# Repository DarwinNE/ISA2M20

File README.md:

# ISA2M20
Adapter for 8-bit ISA card for the Olivetti M20

This project is dedicated to an adapter that allows to connect 8 bit ISA boards to
the bus of an Olivetti M20. Yes, we are talking about 1982 technology.
That may allow to do some nice stuff on the M20 as long as you are able to write the
software for the cards you want to attach.

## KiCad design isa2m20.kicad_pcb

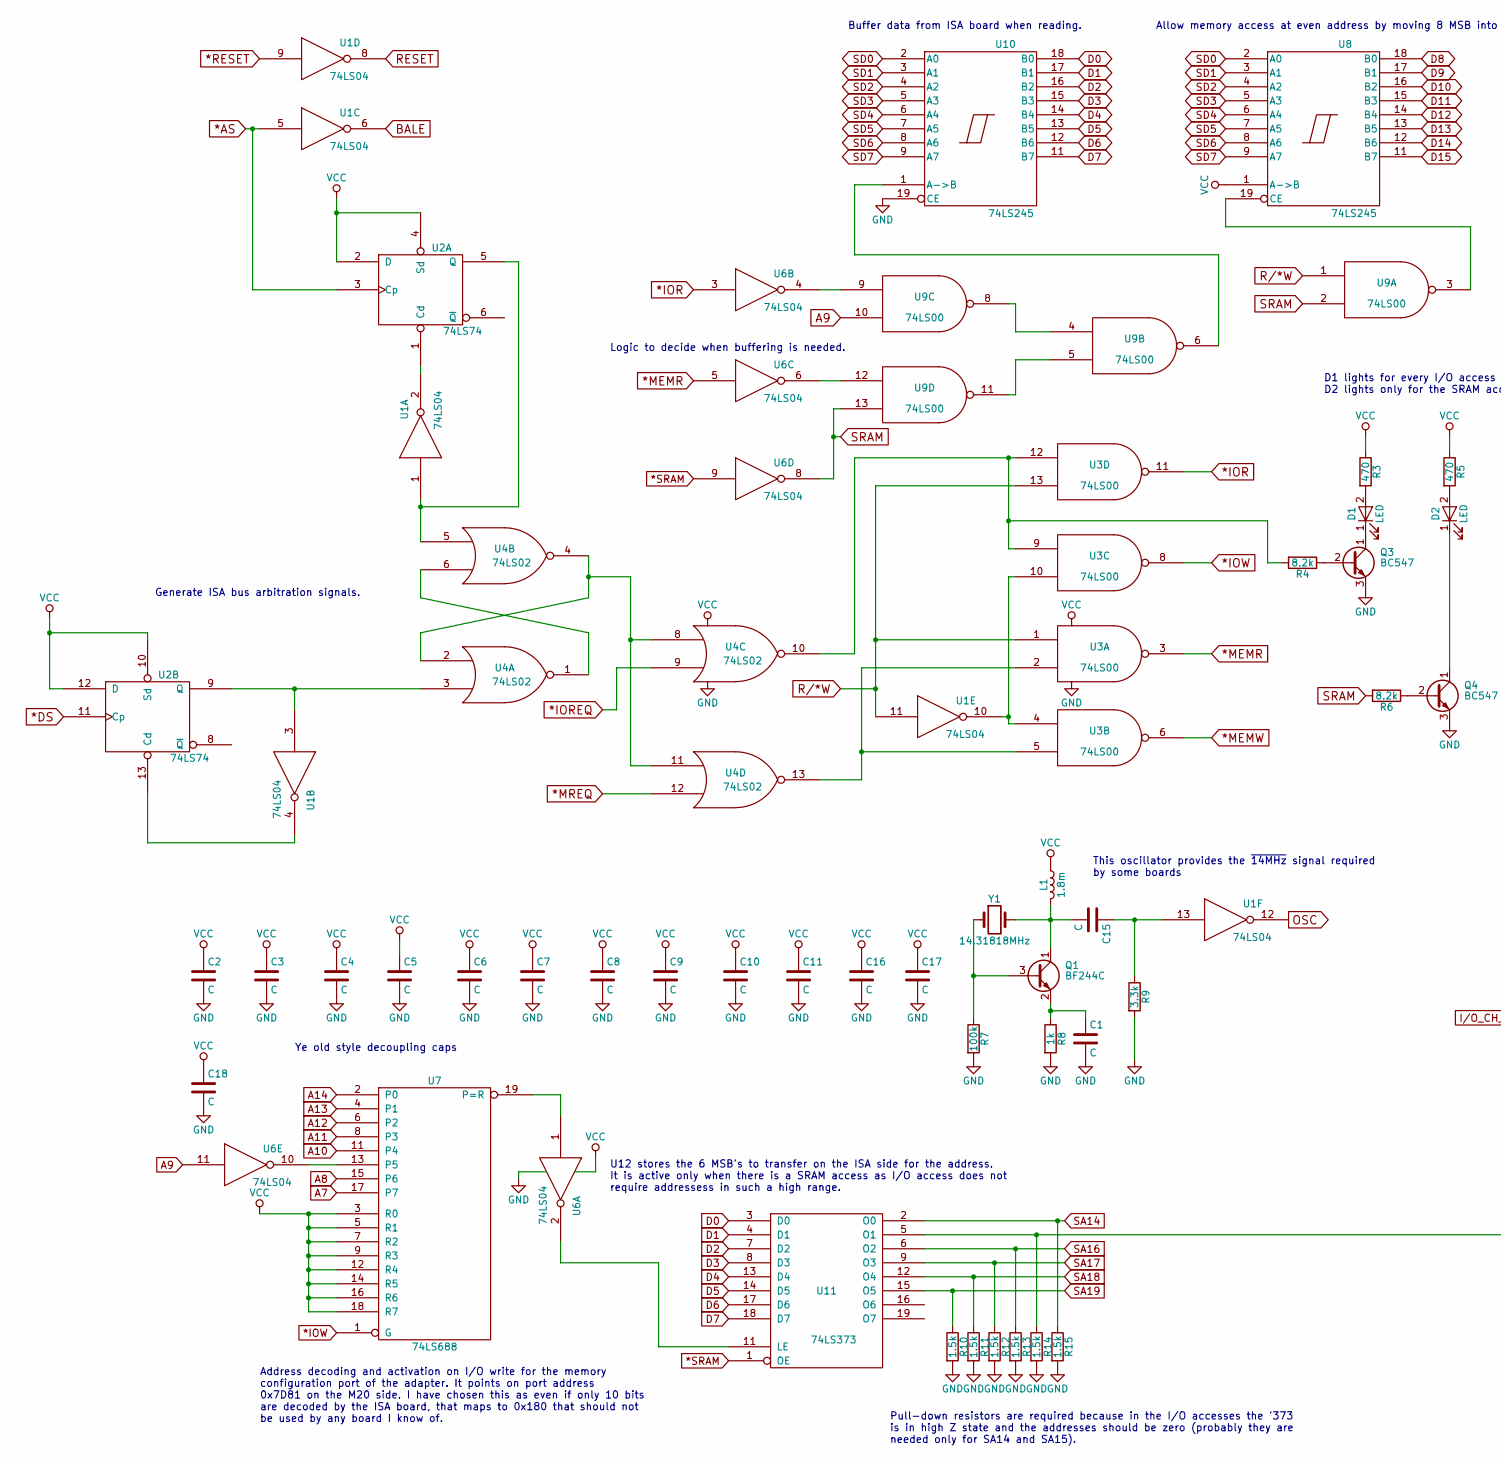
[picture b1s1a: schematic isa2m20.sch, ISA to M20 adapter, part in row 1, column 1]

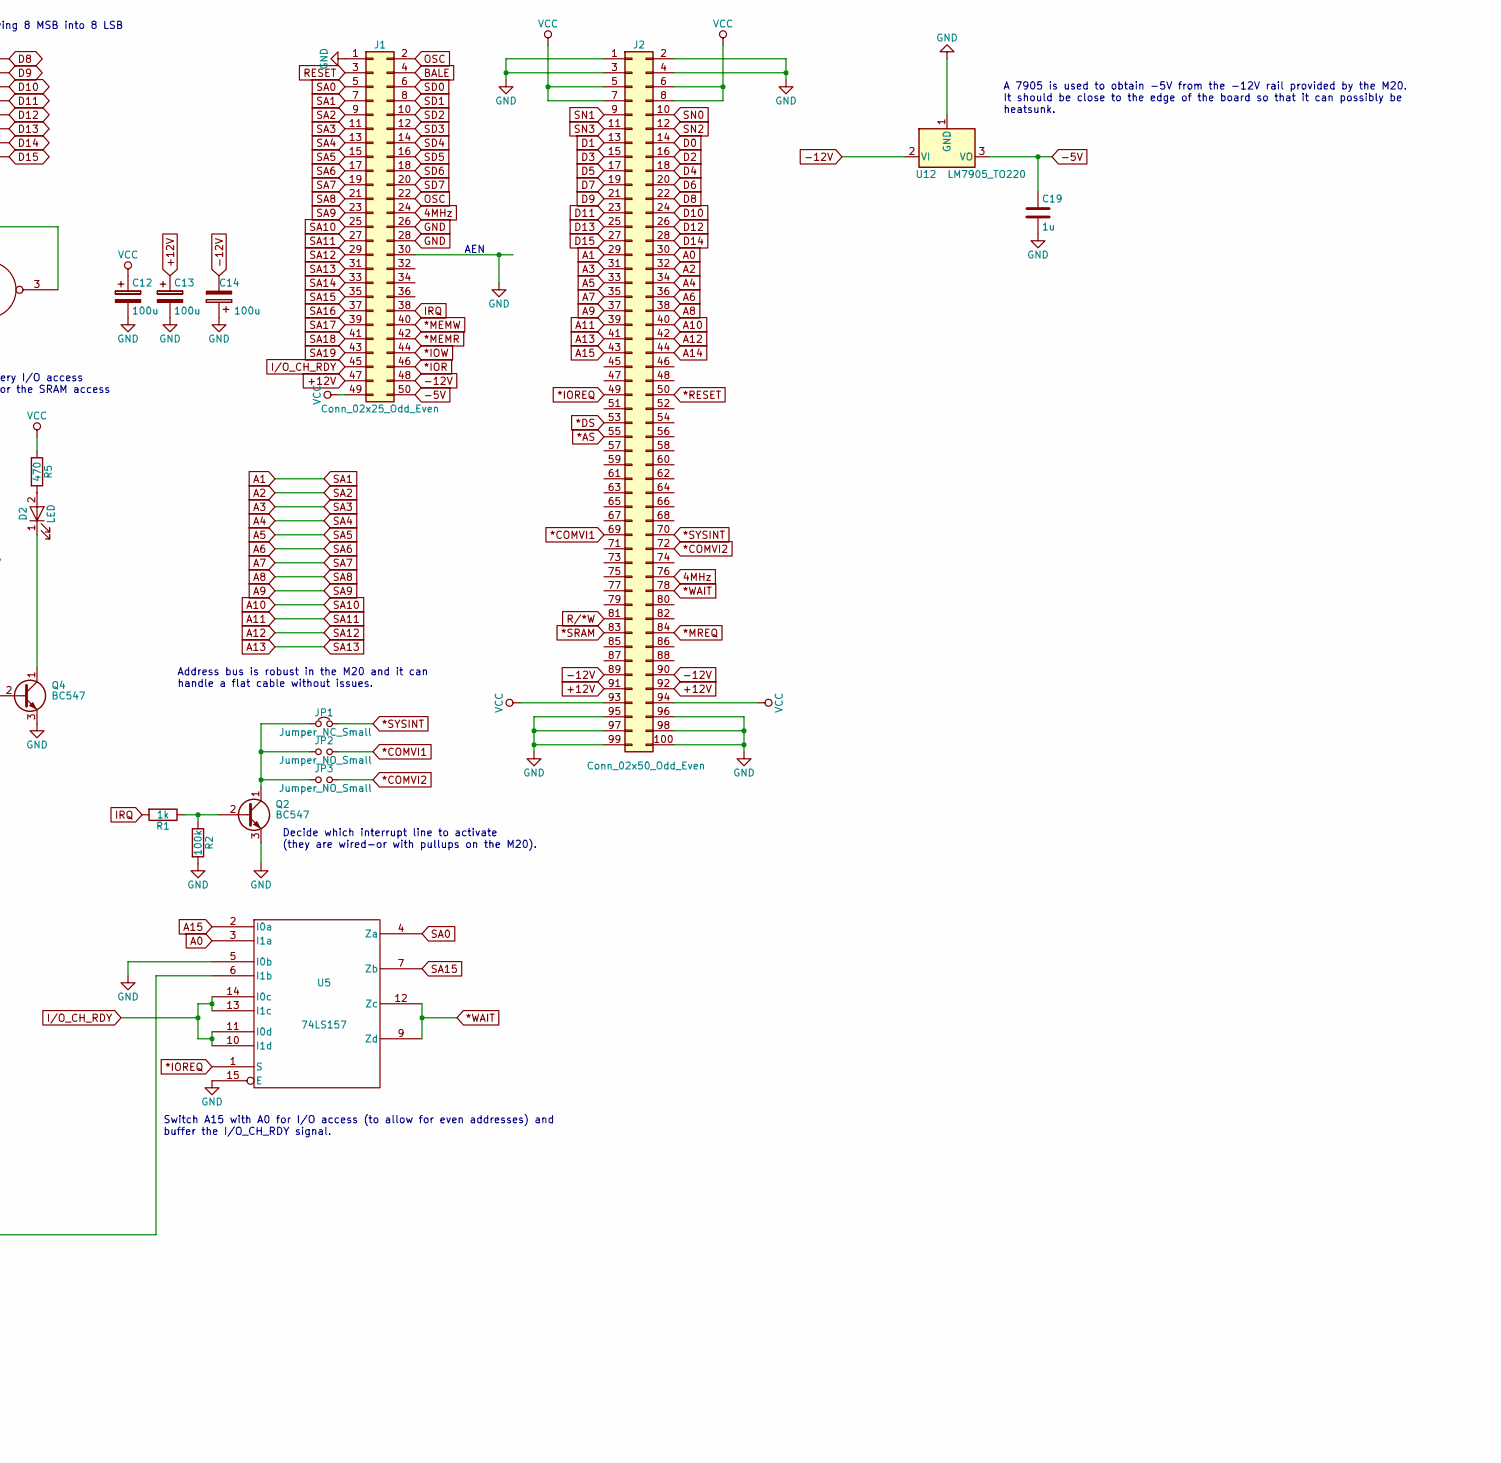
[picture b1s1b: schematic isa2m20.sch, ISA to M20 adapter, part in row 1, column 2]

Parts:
C1: C; C_Axial_L5.1mm_D3.1mm_P7.50mm_Horizontal
C2, C3, C4, C5, C6, C7, C8, C9, C10, C11, C15, C16, C17, C18: C; C_Rect_L9.0mm_W2.5mm_P7.50mm_MKT
C12, C13, C14: 100u; CP_Radial_D10.0mm_P5.00mm
C19: 1u; C_Rect_L9.0mm_W2.5mm_P7.50mm_MKT
D1, D2: LED; LED_D3.0mm
J1: Conn_02x25_Odd_Even; Multicomp_MC9A12-5034_2x25x2.54mm_Straight
J2: Conn_02x50_Odd_Even; 2x50pin_PCB_edge_connector
JP1: Jumper_NC_Small; Socket_Strip_Straight_1x02_Pitch2.54mm
JP2, JP3: Jumper_NO_Small; Socket_Strip_Straight_1x02_Pitch2.54mm
L1: 1.8m; L_Radial_D7.5mm_P5.00mm_Fastron_07P
Q1: BF244C; TO-92_Molded_Narrow
Q2, Q3, Q4: BC547; TO-92_Molded_Narrow
R1, R8: 1k; R_Axial_DIN0207_L6.3mm_D2.5mm_P7.62mm_Horizontal
R2, R7: 100k; R_Axial_DIN0207_L6.3mm_D2.5mm_P7.62mm_Horizontal
R3, R5: 470; R_Axial_DIN0207_L6.3mm_D2.5mm_P7.62mm_Horizontal
R4, R6: 8.2k; R_Axial_DIN0207_L6.3mm_D2.5mm_P7.62mm_Horizontal
R9: 3.3k; R_Axial_DIN0207_L6.3mm_D2.5mm_P7.62mm_Horizontal
R10, R11, R12, R13, R14, R15: 1.5k; R_Axial_DIN0207_L6.3mm_D2.5mm_P7.62mm_Horizontal
U1, U6: 74LS04; DIP-14_W7.62mm_Socket_LongPads
U2: 74LS74; DIP-14_W7.62mm_Socket_LongPads
U3, U9: 74LS00; DIP-14_W7.62mm_Socket_LongPads
U4: 74LS02; DIP-14_W7.62mm_Socket_LongPads
U5: 74LS157; DIP-16_W7.62mm_Socket_LongPads
U7: 74LS688; DIP-20_W7.62mm_Socket_LongPads
U8, U10: 74LS245; DIP-20_W7.62mm_Socket_LongPads
U11: 74LS373; DIP-20_W7.62mm_Socket_LongPads
U12: LM7905_TO220; TO-220-3_Vertical
Y1: 14.31818MHz; Crystal_HC18-U_Vertical

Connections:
4MHz: J1.24, J2.76
*AS: J2.55, U1.5, U2.3 (Cp)
*COMVI1: J2.69, JP2.2
*COMVI2: J2.72, JP3.2
*DS: J2.53, U2.11 (Cp)
*IOR: J1.46, U3.11, U6.3
*IOREQ: J2.49, U4.9, U5.1 (S)
*IOW: J1.44, U3.8, U7.1 (G)
*MEMR: J1.42, U3.3, U6.5
*MEMW: J1.40, U3.6
*MREQ: J2.84, U4.12
*RESET: J2.50, U1.9
*SRAM: J2.83, U6.9, U11.1 (OE)
*SYSINT: J2.70, JP1.2
*WAIT: J2.78, U5.9 (Zd), U5.12 (Zc)
+12V: C13.1, J1.47, J2.91, J2.92
-5V: C19.1, J1.50, U12.3 (VO)
-12V: C14.2, J1.48, J2.89, J2.90, U12.2 (VI)
A0: J2.30, U5.3 (I1a)
A1: J1.7, J2.29
A2: J1.9, J2.32
A3: J1.11, J2.31
A4: J1.13, J2.34
A5: J1.15, J2.33
A6: J1.17, J2.36
A7: J1.19, J2.35, U7.17 (P7)
A8: J1.21, J2.38, U7.15 (P6)
A9: J1.23, J2.37, U6.11, U9.10
A10: J1.25, J2.40, U7.11 (P4)
A11: J1.27, J2.39, U7.8 (P3)
A12: J1.29, J2.42, U7.6 (P2)
A13: J1.31, J2.41, U7.4 (P1)
A14: J2.44, U7.2 (P0)
A15: J2.43, U5.2 (I0a)
BALE: J1.4, U1.6
D0: J2.14, U10.18 (B0), U11.3 (D0)
D1: J2.13, U10.17 (B1), U11.4 (D1)
D2: J2.16, U10.16 (B2), U11.7 (D2)
D3: J2.15, U10.15 (B3), U11.8 (D3)
D4: J2.18, U10.14 (B4), U11.13 (D4)
D5: J2.17, U10.13 (B5), U11.14 (D5)
D6: J2.20, U10.12 (B6), U11.17 (D6)
D7: J2.19, U10.11 (B7), U11.18 (D7)
D8: J2.22, U8.18 (B0)
D9: J2.21, U8.17 (B1)
D10: J2.24, U8.16 (B2)
D11: J2.23, U8.15 (B3)
D12: J2.26, U8.14 (B4)
D13: J2.25, U8.13 (B5)
D14: J2.28, U8.12 (B6)
D15: J2.27, U8.11 (B7)
GND: C1.2, C2.2, C3.2, C4.2, C5.2, C6.2, C7.2, C8.2, C9.2, C10.2, C11.2, C12.2, C13.2, C14.1, C16.2, C17.2, C18.2, C19.2, J1.1, J1.26, J1.28, J1.30, J2.1, J2.2, J2.3, J2.4, J2.95, J2.96, J2.97, J2.98, J2.99, J2.100, Q2.3 (E), Q3.3 (E), Q4.3 (E), R2.2, R7.2, R8.2, R9.2, R10.2, R11.2, R12.2, R13.2, R14.2, R15.2, U1.7 (GND), U2.7 (GND), U3.7 (GND), U4.7 (GND), U5.5 (I0b), U5.8 (GND), U5.15 (E), U6.7 (GND), U7.10 (GND), U8.10 (GND), U9.7 (GND), U10.10 (GND), U10.19 (CE), U11.10 (GND), U12.1 (GND)
I/O_CH_RDY: J1.45, U5.10 (I1d), U5.11 (I0d), U5.13 (I1c), U5.14 (I0c)
IRQ: J1.38, R1.2
unnamed: C1.1, Q1.2 (E), R8.1
unnamed: C15.1, R9.1, U1.13
unnamed: C15.2, L1.2, Q1.1 (C), Y1.2
unnamed: D1.1 (K), Q3.1 (C)
unnamed: D1.2 (A), R3.2
unnamed: D2.1 (K), Q4.1 (C)
unnamed: D2.2 (A), R5.2
unnamed: JP1.1, JP2.1, JP3.1, Q2.1 (C)
unnamed: Q1.3 (B), R7.1, Y1.1
unnamed: Q2.2 (B), R1.1, R2.1
unnamed: Q3.2 (B), R4.1
unnamed: Q4.2 (B), R6.1
unnamed: R4.2, U3.9, U3.12, U4.10
unnamed: R14.1, U5.6 (I1b), U11.5 (O1)
unnamed: U1.1, U2.5 (Q), U4.5
unnamed: U1.2, U2.1 (Cd)
unnamed: U1.3, U2.9 (Q), U4.3
unnamed: U1.4, U2.13 (Cd)
unnamed: U1.10, U3.4, U3.10
unnamed: U3.2, U3.5, U4.13
unnamed: U4.1, U4.6
unnamed: U4.2, U4.4, U4.8, U4.11
unnamed: U6.1, U7.19 (P=R)
unnamed: U6.4, U9.9
unnamed: U6.6, U9.12
unnamed: U6.10, U7.13 (P5)
unnamed: U8.19 (CE), U9.3
unnamed: U9.4, U9.8
unnamed: U9.5, U9.11
unnamed: U9.6, U10.1 (A->B)
unnamed: U6.2, U11.11 (LE)
OSC: J1.2, J1.22, U1.12
R/*W: J2.81, U1.11, U3.1, U3.13, U9.1
RESET: J1.3, U1.8
SA0: J1.5, U5.4 (Za)
SA14: J1.33, R15.1, U11.2 (O0)
SA15: J1.35, U5.7 (Zb)
SA16: J1.37, R13.1, U11.6 (O2)
SA17: J1.39, R12.1, U11.9 (O3)
SA18: J1.41, R11.1, U11.12 (O4)
SA19: J1.43, R10.1, U11.15 (O5)
SD0: J1.6, U8.2 (A0), U10.2 (A0)
SD1: J1.8, U8.3 (A1), U10.3 (A1)
SD2: J1.10, U8.4 (A2), U10.4 (A2)
SD3: J1.12, U8.5 (A3), U10.5 (A3)
SD4: J1.14, U8.6 (A4), U10.6 (A4)
SD5: J1.16, U8.7 (A5), U10.7 (A5)
SD6: J1.18, U8.8 (A6), U10.8 (A6)
SD7: J1.20, U8.9 (A7), U10.9 (A7)
SN0: J2.10
SN1: J2.9
SN2: J2.12
SN3: J2.11
SRAM: R6.2, U6.8, U9.2, U9.13
VCC: C2.1, C3.1, C4.1, C5.1, C6.1, C7.1, C8.1, C9.1, C10.1, C11.1, C12.1, C16.1, C17.1, C18.1, J1.49, J2.5, J2.6, J2.7, J2.8, J2.93, J2.94, L1.1, R3.1, R5.1, U1.14 (VCC), U2.2 (D), U2.4 (Sd), U2.10 (Sd), U2.12 (D), U2.14 (VCC), U3.14 (VCC), U4.14 (VCC), U5.16 (VCC), U6.14 (VCC), U7.3 (R0), U7.5 (R1), U7.7 (R2), U7.9 (R3), U7.12 (R4), U7.14 (R5), U7.16 (R6), U7.18 (R7), U7.20 (VCC), U8.1 (A->B), U8.20 (VCC), U9.14 (VCC), U10.20 (VCC), U11.20 (VCC)

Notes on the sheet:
A 7905 is used to obtain -5V from the -12V rail provided by the M20. It should be close to the edge of the board so that it can possibly be heatsunk.
This oscillator provides the ~14MHz signal required by some boards
D1 lights for every I/O access D2 lights only for the SRAM access
U12 stores the 6 MSB's to transfer on the ISA side for the address. It is active only when there is a SRAM access as I/O access does not require addressess in such a high range.
Address decoding and activation on I/O write for the memory configuration port of the adapter. It points on port address 0x7D81 on the M20 side. I have chosen this as even if only 10 bits are decoded by the ISA board, that maps to 0x180 that should not be used by any board I know of.
Pull-down resistors are required because in the I/O accesses the '373 is in high Z state and the addresses should be zero (probably they are needed only for SA14 and SA15).
Ye old style decoupling caps
Allow memory access at even address by moving 8 MSB into 8 LSB
Buffer data from ISA board when reading.
Logic to decide when buffering is needed.
Generate ISA bus arbitration signals.
Address bus is robust in the M20 and it can handle a flat cable without issues.
Decide which interrupt line to activate (they are wired-or with pullups on the M20).
Switch A15 with A0 for I/O access (to allow for even addresses) and buffer the I/O_CH_RDY signal.
AEN

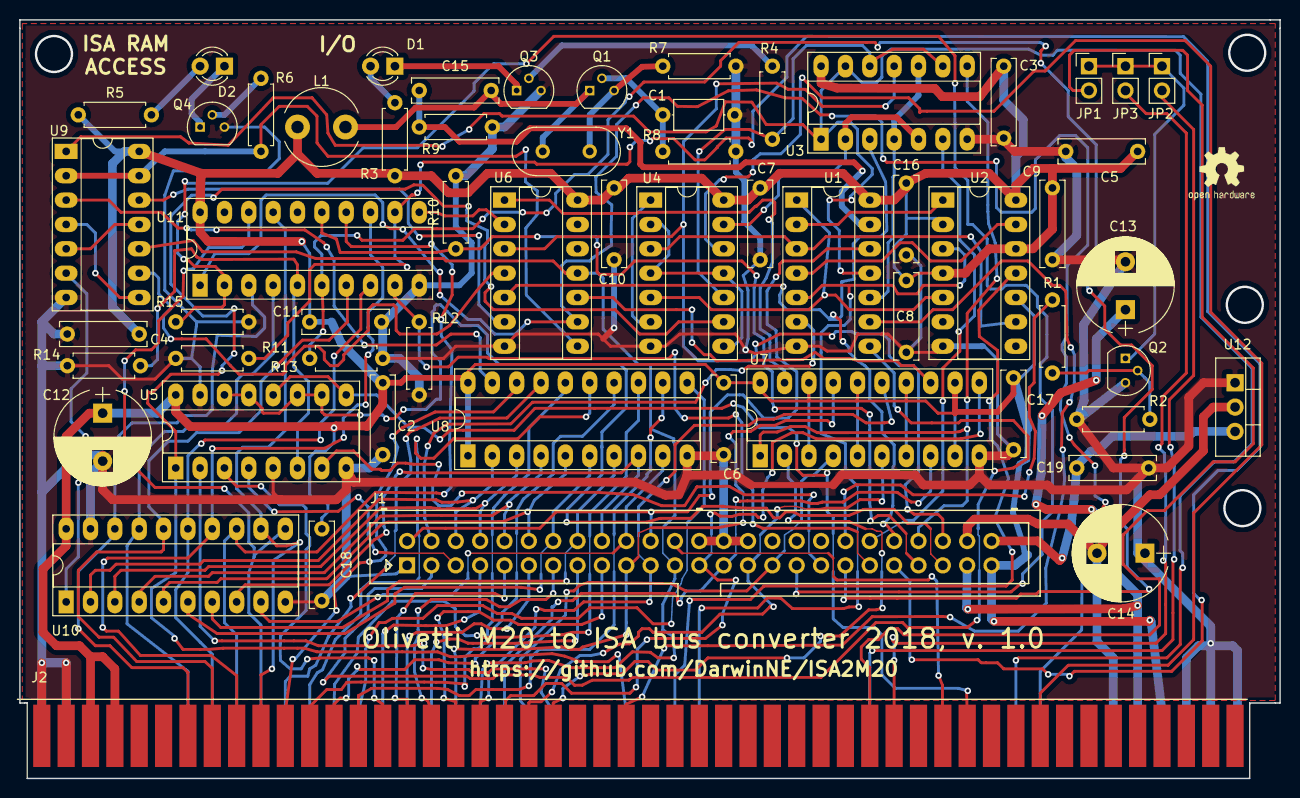
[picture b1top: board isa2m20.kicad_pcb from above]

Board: 2 copper layers, 131.4 x 79.1 mm, 59 parts (0 on the bottom side), 105 nets.

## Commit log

2018-02-26 First version of the ISA2M20 adapter, still to route.
2018-02-26 A little cleanup.
2018-02-26 Modify the configuration I/O address so to avoid potential conflicts with boards decoding only 10 bits on the ISA side.
2018-02-26 Started routing power rails.
2018-02-27 Continue routing.
2018-02-27 The most difficult part remains to be done.
2018-03-01 Continued routing. Quite difficult stage now...
2018-03-05 Continue routing. Quite difficult paths here.
2018-03-05 Routing continues as hard as it gets.
2018-03-06 7 connections remaining, but they are the though ones...
2018-03-06 4 more connections to route.
2018-03-08 Two connections to route.
2018-03-08 Board 100% routed. I still add to beautify the connections and to improve some ugly stuff. There is still some ERC violation to address.
2018-03-10 Beutified a little the card, but still a lot of work remains to be done.
2018-03-11 Tweaked some details.
2018-03-11 Continue to beautify.
